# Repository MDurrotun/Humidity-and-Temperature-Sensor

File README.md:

# Humidity-and-Temperature-Sensor

Monitoring Humidity and Temperature using arduino:
- Arduino nano
- RTC
- LCD 16x2
- DHT 11 - Humidity and temperature sensor

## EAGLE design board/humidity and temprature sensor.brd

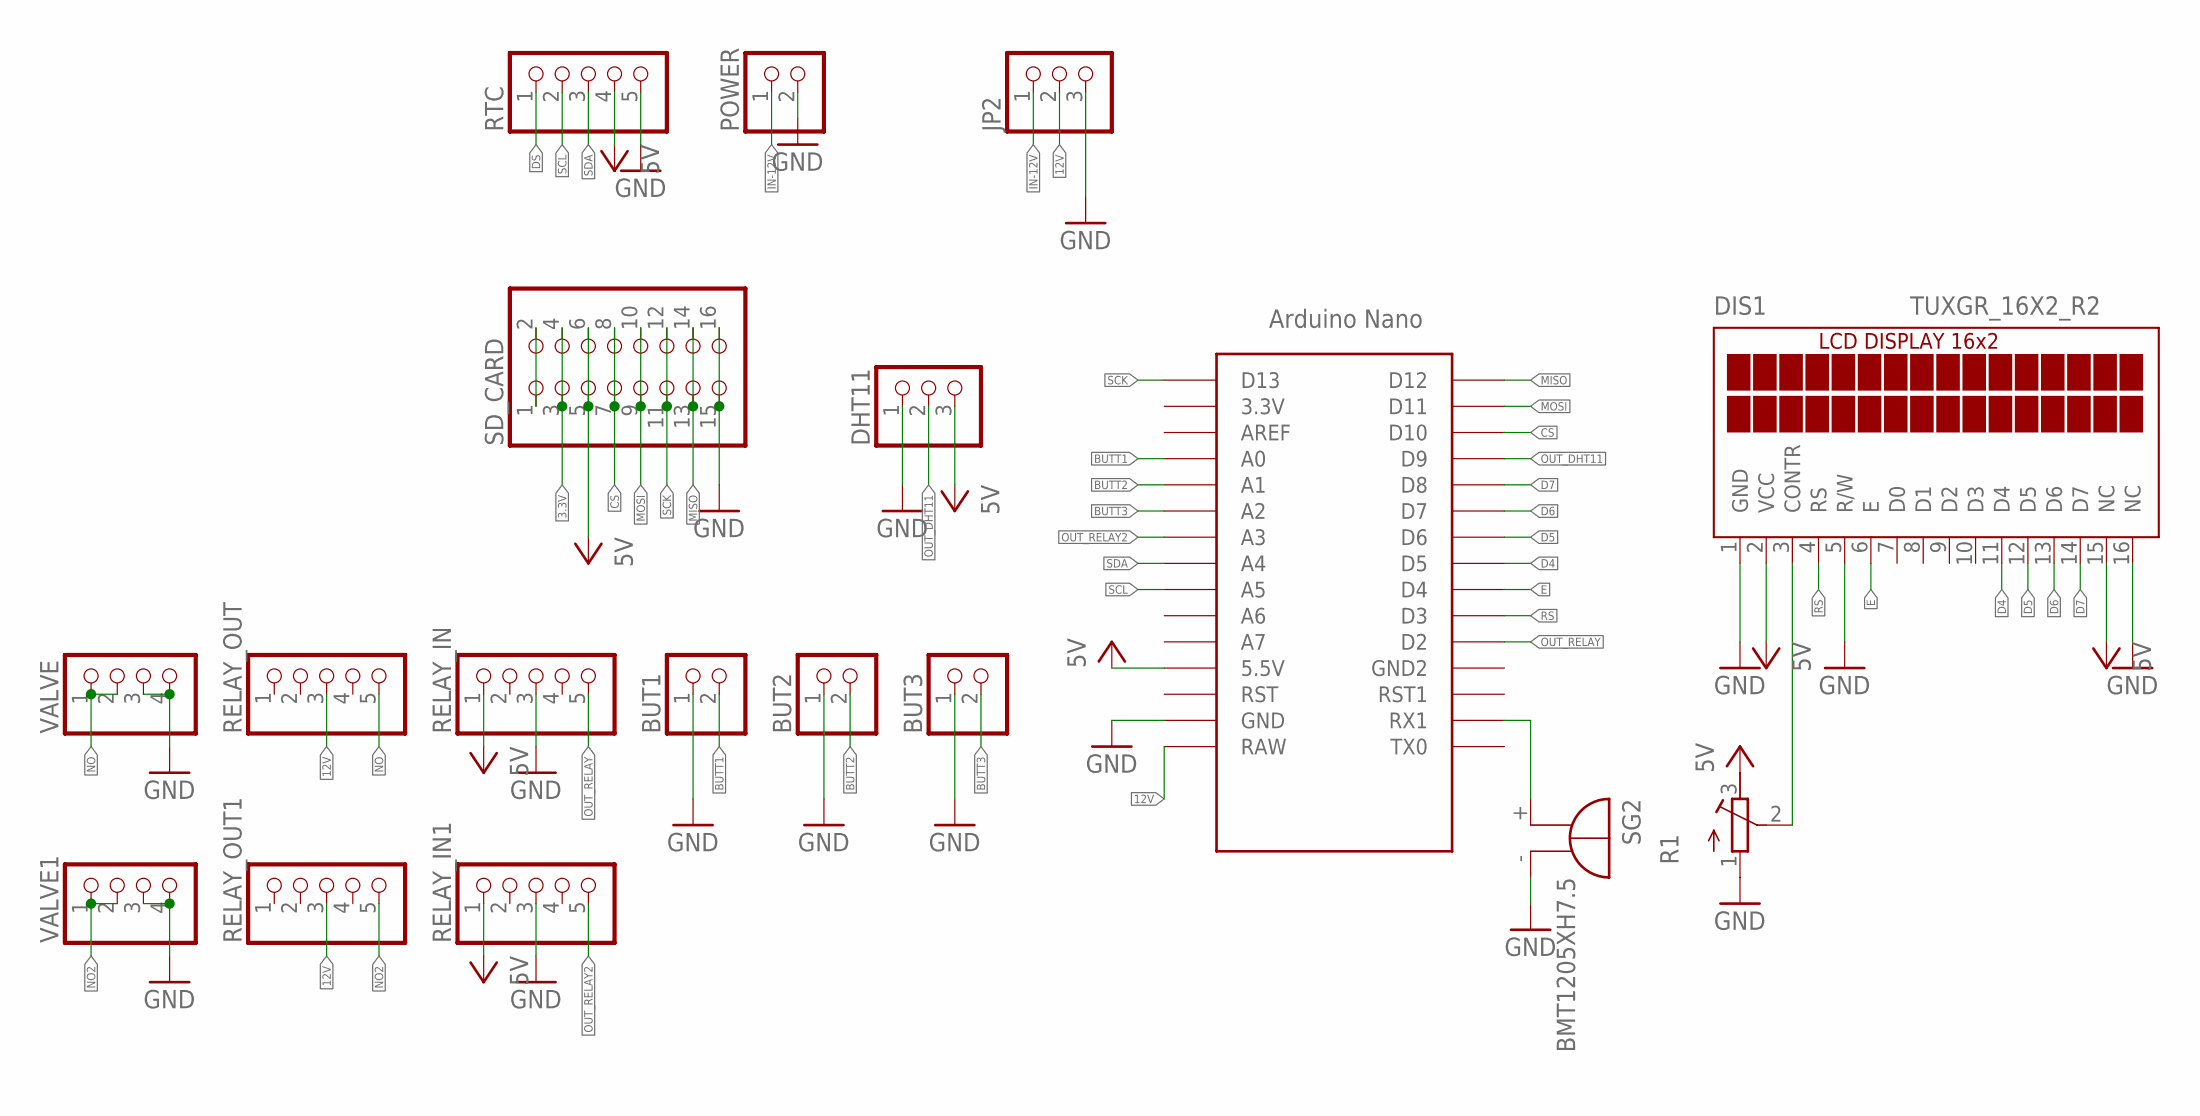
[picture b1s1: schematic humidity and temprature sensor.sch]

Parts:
BUT1, BUT2, BUT3: PINHD-1X2; 1X02
DHT11: PINHD-1X3; 1X03
DIS1: TUXGR_16X2_R2
JP2: PINHD-1X3; 1X03
POWER: PINHD-1X2; 1X02
R1: R-TRIMM3339P; RTRIM3339P
RELAY_IN, RELAY_IN1: PINHD-1X5; 1X05
RELAY_OUT, RELAY_OUT1: PINHD-1X5; 1X05
RTC: PINHD-1X5; 1X05
SD_CARD: PINHD-2X8; 2X08
SG2: BMT1205XH7.5
U$2: NANO
VALVE, VALVE1: PINHD-1X4; 1X04

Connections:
3.3V: SD_CARD.3, SD_CARD.4
12V: JP2.2, RELAY_OUT.3, RELAY_OUT1.3, U$2.RAW
BUTT1: BUT1.2, U$2.A0
BUTT2: BUT2.2, U$2.A1
BUTT3: BUT3.2, U$2.A2
CS: SD_CARD.7, SD_CARD.8, U$2.D10
D4: DIS1.11 (D4), U$2.D5
D5: DIS1.12 (D5), U$2.D6
D6: DIS1.13 (D6), U$2.D7
D7: DIS1.14 (D7), U$2.D8
DS: RTC.1
E: DIS1.6 (E), U$2.D4
GND: BUT1.1, BUT2.1, BUT3.1, DHT11.1, DIS1.1 (GND), DIS1.5 (R/W), DIS1.16 (NC), JP2.3, POWER.2, R1.1 (E), RELAY_IN.3, RELAY_IN1.3, RTC.5, SD_CARD.15, SD_CARD.16, SG2.-, U$2.GND, VALVE.3, VALVE.4, VALVE1.3, VALVE1.4
IN-12V: JP2.1, POWER.1
MISO: SD_CARD.13, SD_CARD.14, U$2.D12
MOSI: SD_CARD.9, SD_CARD.10, U$2.D11
unnamed: SD_CARD.1, SD_CARD.2
unnamed: DIS1.3 (CONTR), R1.2 (S)
unnamed: SG2.+, U$2.RX1
NO: RELAY_OUT.5, VALVE.1, VALVE.2
NO2: RELAY_OUT1.5, VALVE1.1, VALVE1.2
OUT_DHT11: DHT11.2, U$2.D9
OUT_RELAY: RELAY_IN.5, U$2.D2
OUT_RELAY2: RELAY_IN1.5, U$2.A3
RS: DIS1.4 (RS), U$2.D3
SCK: SD_CARD.11, SD_CARD.12, U$2.D13
SCL: RTC.2, U$2.A5
SDA: RTC.3, U$2.A4
VCC: DHT11.3, DIS1.2 (VCC), DIS1.15 (NC), R1.3 (A), RELAY_IN.1, RELAY_IN1.1, RTC.4, SD_CARD.5, SD_CARD.6, U$2.5V (5.5V)

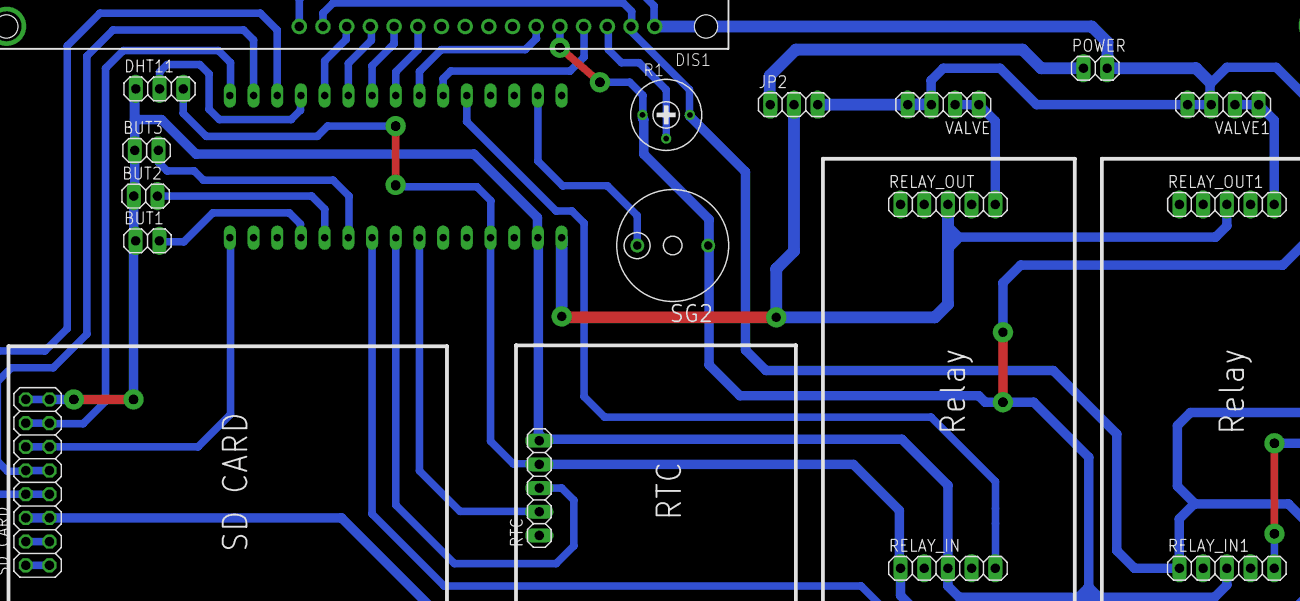
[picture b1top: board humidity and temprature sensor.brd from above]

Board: 2 copper layers, 18 parts (0 on the bottom side), 28 nets.

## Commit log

2019-01-01 Add Main Program and Schematic
